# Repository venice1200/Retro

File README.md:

# Retro
Projects for older Retro Style Systems

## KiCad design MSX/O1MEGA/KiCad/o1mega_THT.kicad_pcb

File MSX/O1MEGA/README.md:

# O1MEGA for Omega MSX  
Space optimized PCB for additional 512KB Ram for the [Omega MSX Computer](https://github.com/skiselev/omega).  
The PCB is based on the [o4mega](https://github.com/msx-solis/o4Mega_v3.2) Board from MSXmakers.  
  
[Schematics](KiCad/o1mega_THT_Schematics.pdf)  
[Gerber ZIP File](KiCad/Gerber.zip)

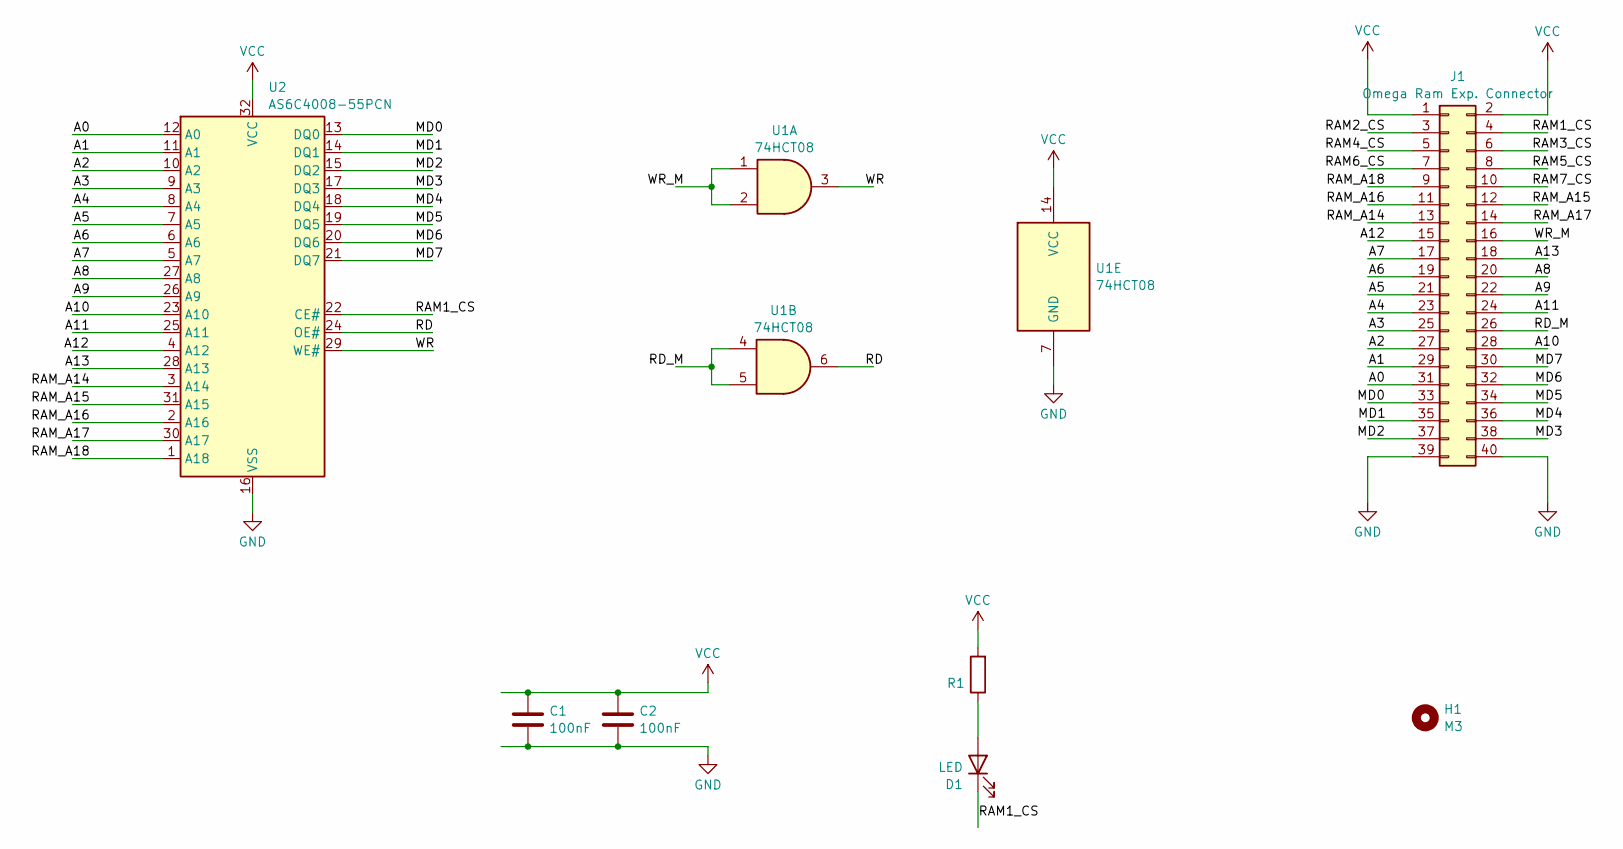
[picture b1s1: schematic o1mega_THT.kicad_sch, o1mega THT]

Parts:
C1, C2: 100nF; C_Disc_D10.0mm_W2.5mm_P5.00mm
D1: LED; LED_D3.0mm
H1: M3; MountingHole_3.2mm_M3
J1: Omega Ram Exp. Connector; PinHeader_2x20_P2.54mm_Vertical
R1: R_Axial_DIN0207_L6.3mm_D2.5mm_P10.16mm_Horizontal
U1: 74HCT08; DIP-14_W7.62mm_Socket_LongPads
U2: AS6C4008-55PCN; DIP-32_W15.24mm_Socket_LongPads

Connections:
/A0: J1.31, U2.12 (A0)
/A1: J1.29, U2.11 (A1)
/A2: J1.27, U2.10 (A2)
/A3: J1.25, U2.9 (A3)
/A4: J1.23, U2.8 (A4)
/A5: J1.21, U2.7 (A5)
/A6: J1.19, U2.6 (A6)
/A7: J1.17, U2.5 (A7)
/A8: J1.20, U2.27 (A8)
/A9: J1.22, U2.26 (A9)
/A10: J1.28, U2.23 (A10)
/A11: J1.24, U2.25 (A11)
/A12: J1.15, U2.4 (A12)
/A13: J1.18, U2.28 (A13)
/MD0: J1.33, U2.13 (DQ0)
/MD1: J1.35, U2.14 (DQ1)
/MD2: J1.37, U2.15 (DQ2)
/MD3: J1.38, U2.17 (DQ3)
/MD4: J1.36, U2.18 (DQ4)
/MD5: J1.34, U2.19 (DQ5)
/MD6: J1.32, U2.20 (DQ6)
/MD7: J1.30, U2.21 (DQ7)
/RAM1_CS: D1.1 (K), J1.4, U2.22 (CE#)
/RAM2_CS: J1.3
/RAM3_CS: J1.6
/RAM4_CS: J1.5
/RAM5_CS: J1.8
/RAM6_CS: J1.7
/RAM7_CS: J1.10
/RAM_A14: J1.13, U2.3 (A14)
/RAM_A15: J1.12, U2.31 (A15)
/RAM_A16: J1.11, U2.2 (A16)
/RAM_A17: J1.14, U2.30 (A17)
/RAM_A18: J1.9, U2.1 (A18)
/RD: U1.6, U2.24 (OE#)
/RD_M: J1.26, U1.4, U1.5
/WR: U1.3, U2.29 (WE#)
/WR_M: J1.16, U1.1, U1.2
GND: C1.2, C2.2, J1.39, J1.40, U1.7 (GND), U2.16 (VSS)
unnamed: D1.2 (A), R1.1
VCC: C1.1, C2.1, J1.1, J1.2, R1.2, U1.14 (VCC), U2.32 (VCC)

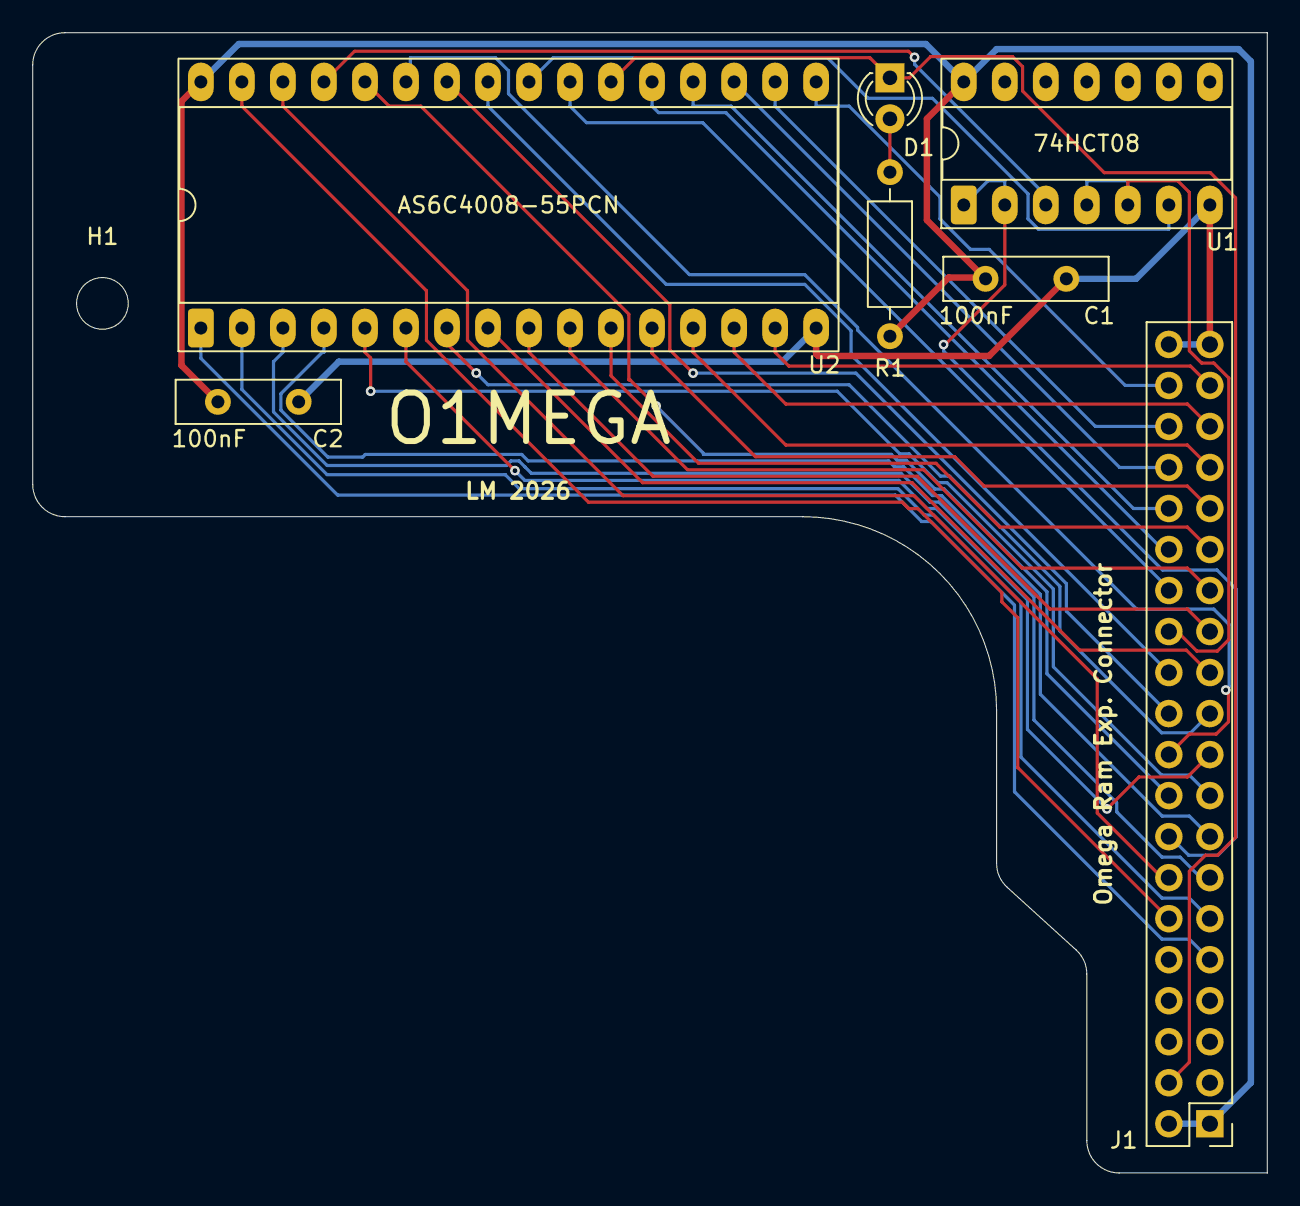
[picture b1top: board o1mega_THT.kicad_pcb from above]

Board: 2 copper layers, 76.5 x 70.6 mm, 8 parts (0 on the bottom side), 35 nets.

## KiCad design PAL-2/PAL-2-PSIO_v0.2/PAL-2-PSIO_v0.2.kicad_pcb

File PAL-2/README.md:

# PAL-2  
Two IO Board Projects for the PAL-2 System.  
Similar features, different Layout.  
Based on PAL-2 PSU by Dieter Baron https://github.com/T-Pau/PAL-2-PSU
  
Pins for USB Serial, PA0-7 , PB0-7 (PB6 need a PAL-2 mod) and DecEn,  
TTY & KBD Switch, RS232 (using MAX202) & USB Serial Switch,  
Switch for RS232 Straight & Nullmodem Mode,  
Jumper/Solder Jumper for RS232 Mode, PB6 and DecEn.  
IO Block Layout compatible with PAL-1 Add-On Boards.  
  
3-Way Switch for USB or DC Barrel Connector Power.  
  
v0.1 (PA/PB IO at bottom)  

v0.2 (PA/PB IO at side)

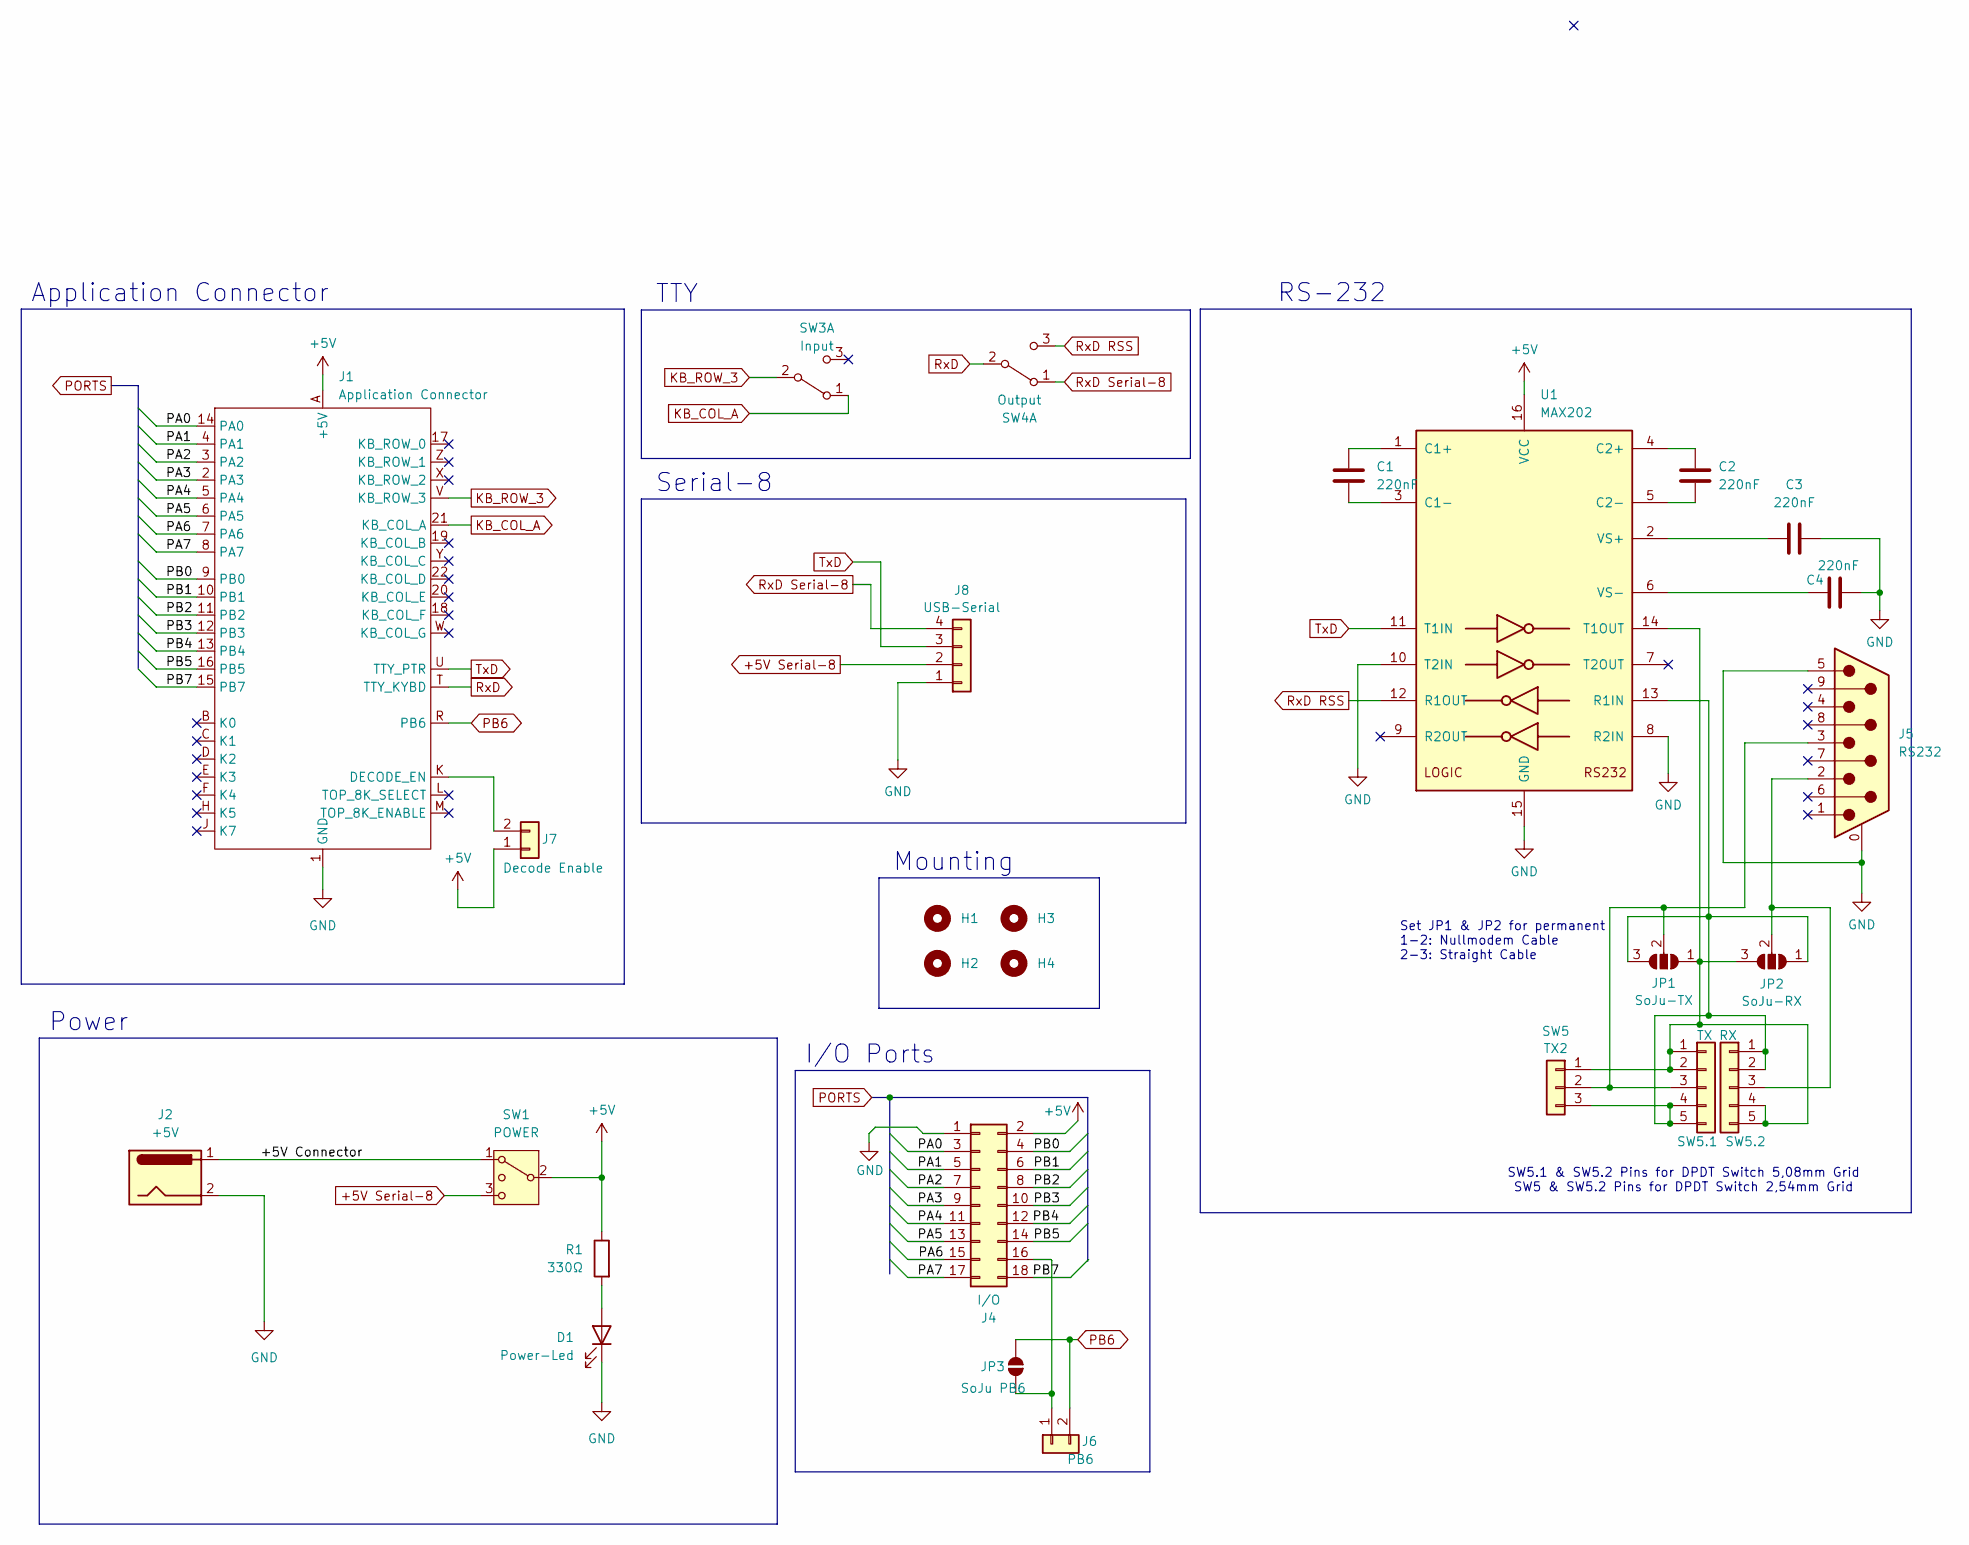
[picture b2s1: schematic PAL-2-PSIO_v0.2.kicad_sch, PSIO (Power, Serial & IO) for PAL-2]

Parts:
C1, C2, C3, C4: 220nF; C_Disc_D5.0mm_W2.5mm_P5.00mm
D1: Power-Led; LED_D5.0mm
H1, H2, H3, H4: MountingHole_3.2mm_M3
J1: Application Connector; PAL-2 Connector
J2: +5V; BarrelJack_Horizontal
J4: I/O; PinHeader_2x09_P2.54mm_Horizontal
J5: RS232; DSUB-9_Male_Horizontal_P2.77x2.84mm_EdgePinOffset4.94mm_Hou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
J6: PB6; PinHeader_1x02_P2.54mm_Vertical
J7: Decode Enable; PinHeader_1x02_P2.54mm_Vertical
J8: USB-Serial; PinHeader_2x02_P2.54mm_Horizontal
JP1: SoJu-TX; SolderJumper-3_P1.3mm_Open_RoundedPad1.0x1.5mm
JP2: SoJu-RX; SolderJumper-3_P1.3mm_Open_RoundedPad1.0x1.5mm
JP3: SoJu PB6; SolderJumper-2_P1.3mm_Open_RoundedPad1.0x1.5mm
R1: 330Ω; R_Axial_DIN0309_L9.0mm_D3.2mm_P12.70mm_Horizontal
SW1: POWER; SS2513
SW3: Input; SS2513
SW4: Output; SS2513
SW5: TX2; PinHeader_1x03_P2.54mm_Vertical
SW5.1: TX; PinHeader_1x05_P2.54mm_Vertical
SW5.2: RX; PinHeader_1x05_P2.54mm_Vertical
U1: MAX202; DIP-16_W7.62mm_Socket_LongPads

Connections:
+5V: J1.A (+5V), J4.2, J7.1, R1.1, SW1.2 (3), U1.16 (VCC)
+5V Serial-8: J8.2, SW1.3 (4)
/+5V Connector: J2.1, SW1.1
/PA0: J1.14 (PA0), J4.3
/PA1: J1.4 (PA1), J4.5
/PA2: J1.3 (PA2), J4.7
/PA3: J1.2 (PA3), J4.9
/PA4: J1.5 (PA4), J4.11
/PA5: J1.6 (PA5), J4.13
/PA6: J1.7 (PA6), J4.15
/PA7: J1.8 (PA7), J4.17
/PB0: J1.9 (PB0), J4.4
/PB1: J1.10 (PB1), J4.6
/PB2: J1.11 (PB2), J4.8
/PB3: J1.12 (PB3), J4.10
/PB4: J1.13 (PB4), J4.12
/PB5: J1.16 (PB5), J4.14
/PB7: J1.15 (PB7), J4.18
GND: C3.1, C4.1, D1.1 (K), J1.1 (GND), J2.2, J4.1, J5.0 (PAD), J5.5, J8.1, U1.8 (R2IN), U1.10 (T2IN), U1.15 (GND)
KB_COL_A: J1.21 (KB_COL_A), SW3.1 (A)
KB_ROW_3: J1.V (KB_ROW_3), SW3.2 (B)
unnamed: D1.2 (A), R1.2
unnamed: J1.K (DECODE_EN), J7.2
unnamed: J4.16, J6.1, JP3.1 (A)
unnamed: JP1.1 (A), JP2.3 (B), SW5.1, SW5.1.1, SW5.1.2, SW5.2.4, SW5.2.5, U1.14 (T1OUT)
unnamed: JP1.3 (B), JP2.1 (A), SW5.3, SW5.1.4, SW5.1.5, SW5.2.1, SW5.2.2, U1.13 (R1IN)
unnamed: J5.3, JP1.2 (C), SW5.2, SW5.1.3
unnamed: J5.2, JP2.2 (C), SW5.2.3
unnamed: C1.1, U1.1 (C1+)
unnamed: C1.2, U1.3 (C1-)
unnamed: C2.1, U1.4 (C2+)
unnamed: C2.2, U1.5 (C2-)
unnamed: C3.2, U1.2 (VS+)
unnamed: C4.2, U1.6 (VS-)
PB6: J1.R (PB6), J6.2, JP3.2 (B)
RxD: J1.T (TTY_KYBD), SW4.2 (B)
RxD RSS: SW4.3 (C), U1.12 (R1OUT)
RxD Serial-8: J8.4, SW4.1 (A)
TxD: J1.U (TTY_PTR), J8.3, U1.11 (T1IN)

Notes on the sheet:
Mounting
SW5.1 & SW5.2 Pins for DPDT Switch 5,08mm Grid SW5 & SW5.2 Pins for DPDT Switch 2,54mm Grid
Set JP1 & JP2 for permanent 1-2: Nullmodem Cable 2-3: Straight Cable
TTY
Power
Application Connector
Serial-8
RS-232
I/O Ports

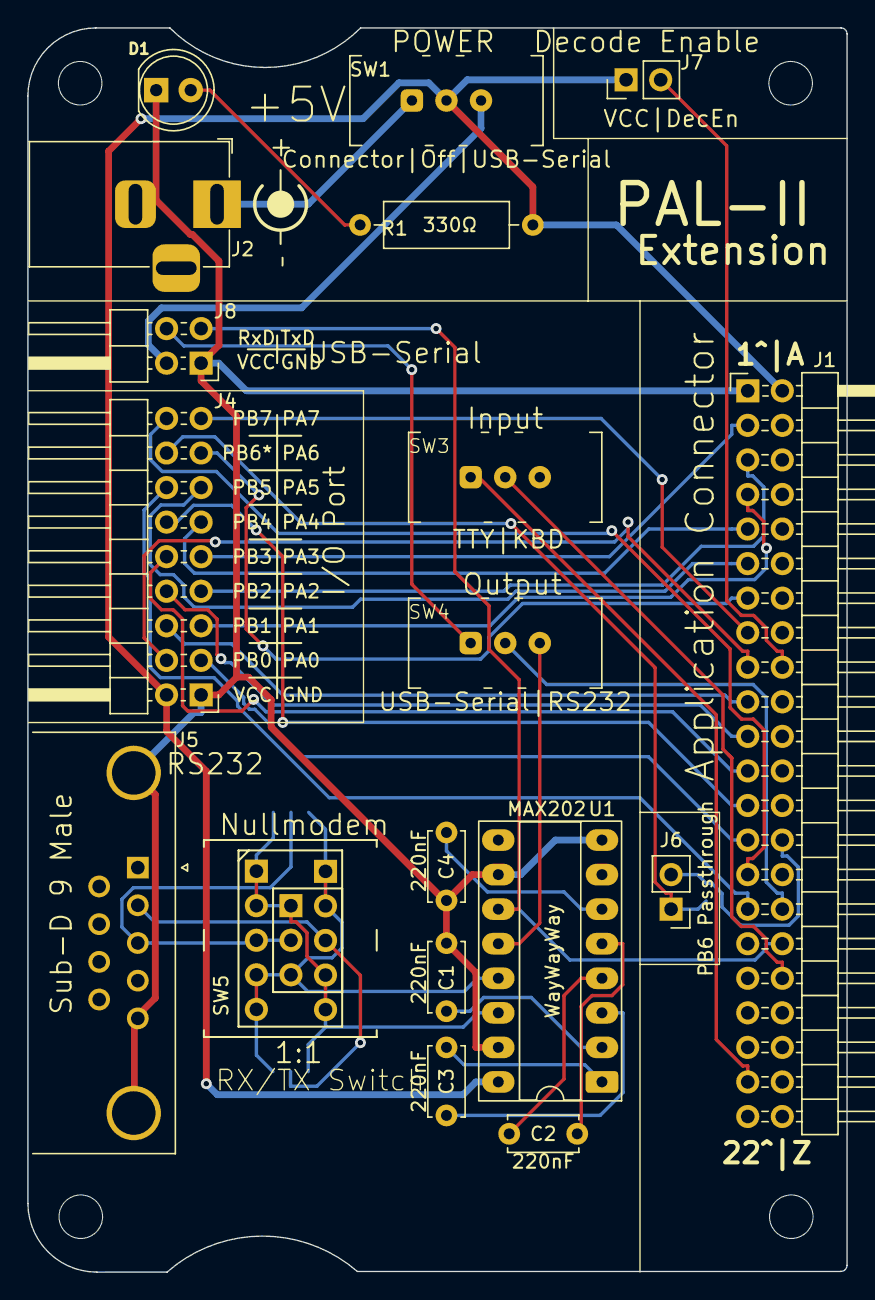
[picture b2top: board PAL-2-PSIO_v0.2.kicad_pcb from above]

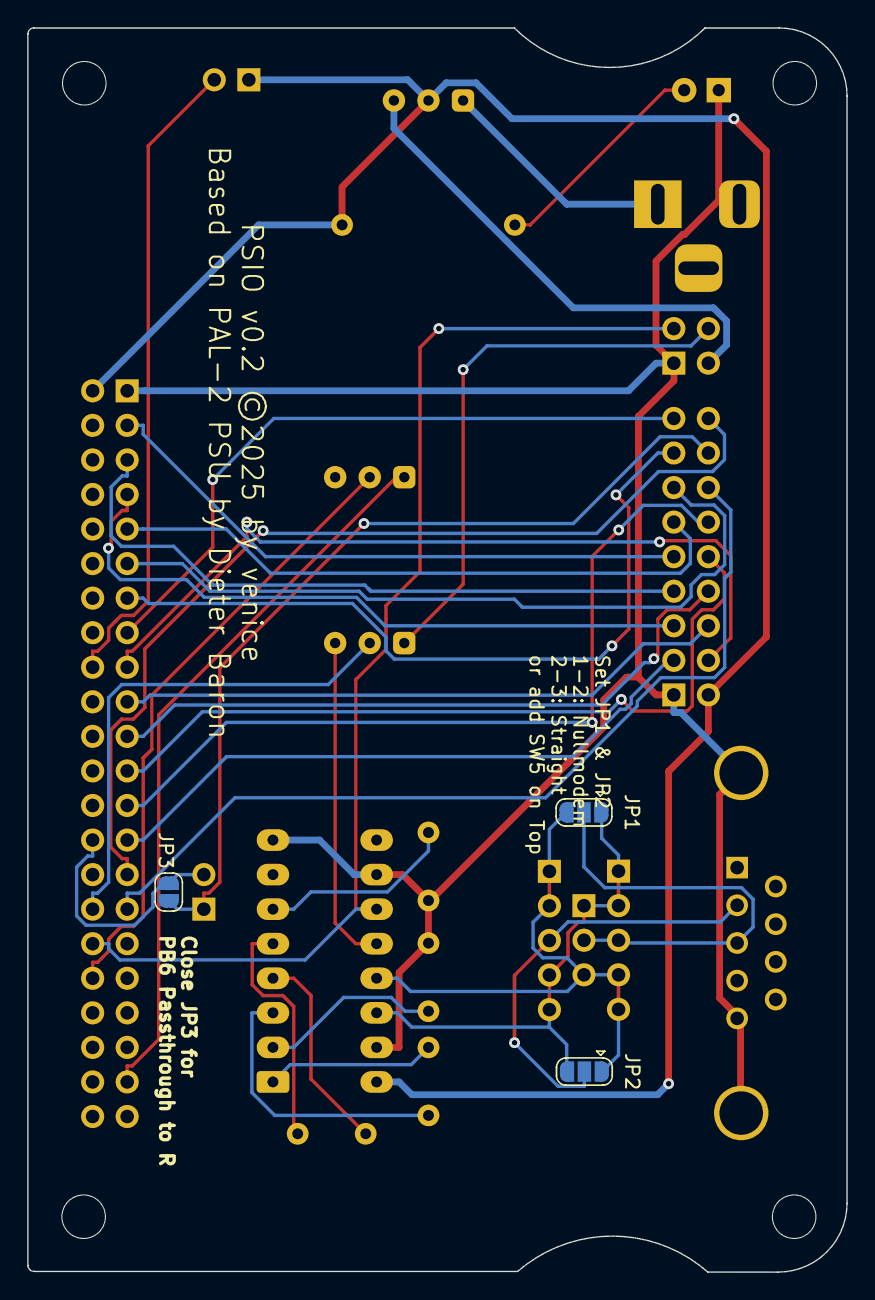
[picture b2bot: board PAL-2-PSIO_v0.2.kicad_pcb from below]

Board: 2 copper layers, 60.2 x 91.5 mm, 27 parts (3 on the bottom side), 39 nets.

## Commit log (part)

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2024-04-16 Add Amiga STLs
    ...for the A500 Plexilaser Case
2024-04-16 Adding C64 STLs
    ...for an WS2812 LED
2024-04-16 Re-Order
2025-08-14 First Release
2025-08-14 Update Docs
2025-09-07 Enhance the Arduino Sketch with a RND Generator
2025-09-08 README.md aktualisieren
2026-03-12 Upload PAL_PSIO v0.1+v0.2
2026-03-12 Picture Update
2026-03-12 Cleanup Part 1
2026-03-12 Cleanup Parft 2

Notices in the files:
PAL-2/PAL-2-PSIO_v0.2/PAL-2-PSIO_v0.2.kicad_pcb:
PSIO v0.2 ©2025 by venice
